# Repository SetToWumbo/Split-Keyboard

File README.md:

TODO:

 - update to version 0.0.1 where pcb design is no longer reversible to help in learning basics
 - remove top row from possible switches and update accordingly:
        *start with removing the inner thumb modifier position*

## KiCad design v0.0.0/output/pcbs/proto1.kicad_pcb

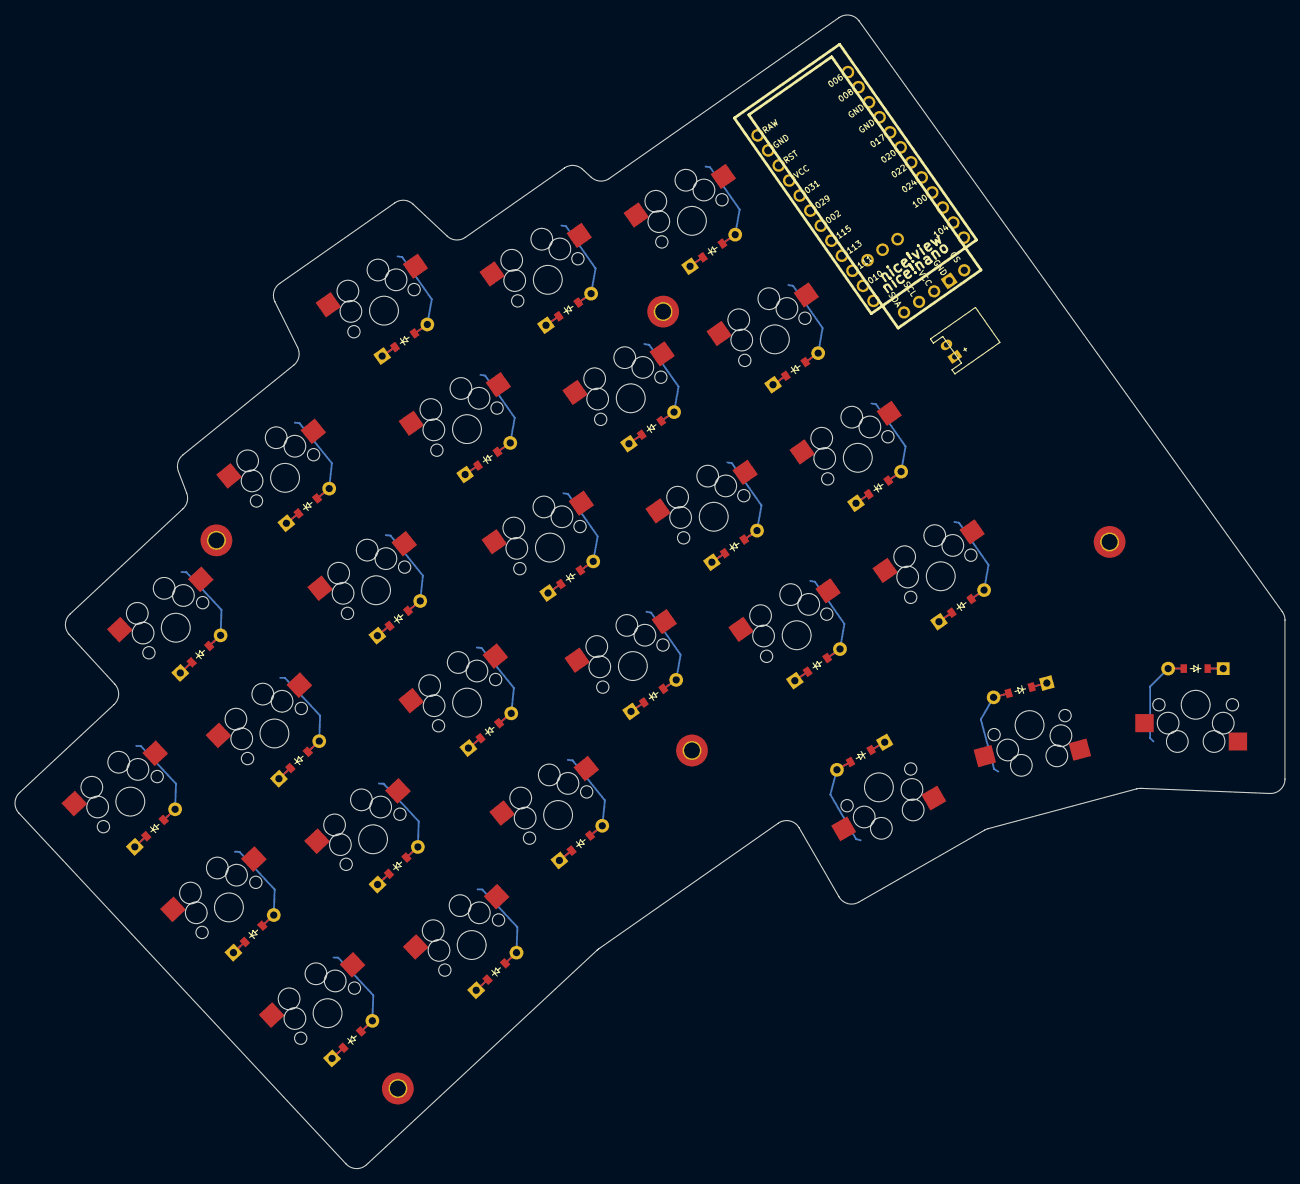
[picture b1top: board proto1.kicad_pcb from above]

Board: 2 copper layers, 175.6 x 159.5 mm, 60 parts (0 on the bottom side), 42 nets.

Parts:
D1, D2, D3, D4, D5, D6, D7, D8, D9, D10, D11, D12, D13, D14, D15, D16, D17, D18, D19, D20, D21, D22, D23, D24, D25, D26: ComboDiode
JST1: JST_PH_S2B-PH-K_02x2.00mm_Angled
MCU1: nice_nano
S1, S2, S3, S4, S5, S6, S7, S8, S9, S10, S11, S12, S13, S14, S15, S16, S17, S18, S19, S20, S21, S22, S23, S24, S25, S26: MX
_1, _2, _3, _4, _5: HOLE_M2
niceView1: niceView; niceView_headers

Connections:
GND: JST1.2, MCU1.3, MCU1.4, MCU1.23, niceView1.2
P002: D1.1, D5.1, D9.1, D13.1, D17.1, D21.1, MCU1.18
P006: MCU1.1, niceView1.1
P008: MCU1.2, S20.1, S21.1, S22.1, S23.1, S26.1
P009: MCU1.13, S12.1, S13.1, S14.1, S15.1, S24.1
P010: MCU1.14, S8.1, S9.1, S10.1, S11.1
P024: MCU1.8, niceView1.4
P029: D2.1, D6.1, D10.1, D14.1, D18.1, D22.1, MCU1.19
P031: D3.1, D7.1, D11.1, D15.1, D19.1, D23.1, MCU1.20
P100: MCU1.9, niceView1.5
P104: MCU1.11, S16.1, S17.1, S18.1, S19.1, S25.1
P106: D24.1, D25.1, D26.1, MCU1.12
P111: MCU1.15, S4.1, S5.1, S6.1, S7.1
P113: MCU1.16, S1.1, S2.1, S3.1
P115: D4.1, D8.1, D12.1, D16.1, D20.1, MCU1.17
VCC: JST1.1, MCU1.21, niceView1.3
index_bottom: D16.2, S16.2
index_home: D17.2, S17.2
index_num: D18.2, S18.2
index_top: D19.2, S19.2
inner_bottom: D20.2, S20.2
inner_home: D21.2, S21.2
inner_num: D22.2, S22.2
inner_top: D23.2, S23.2
layer2_cluster: D25.2, S25.2
layer_cluster: D24.2, S24.2
middle_bottom: D12.2, S12.2
middle_home: D13.2, S13.2
middle_num: D14.2, S14.2
middle_top: D15.2, S15.2
outer_home: D1.2, S1.2
outer_num: D2.2, S2.2
outer_top: D3.2, S3.2
pinky_bottom: D4.2, S4.2
pinky_home: D5.2, S5.2
pinky_num: D6.2, S6.2
pinky_top: D7.2, S7.2
ring_bottom: D8.2, S8.2
ring_home: D9.2, S9.2
ring_num: D10.2, S10.2
ring_top: D11.2, S11.2
space_cluster: D26.2, S26.2

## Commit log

2025-03-13 footprint generator library
